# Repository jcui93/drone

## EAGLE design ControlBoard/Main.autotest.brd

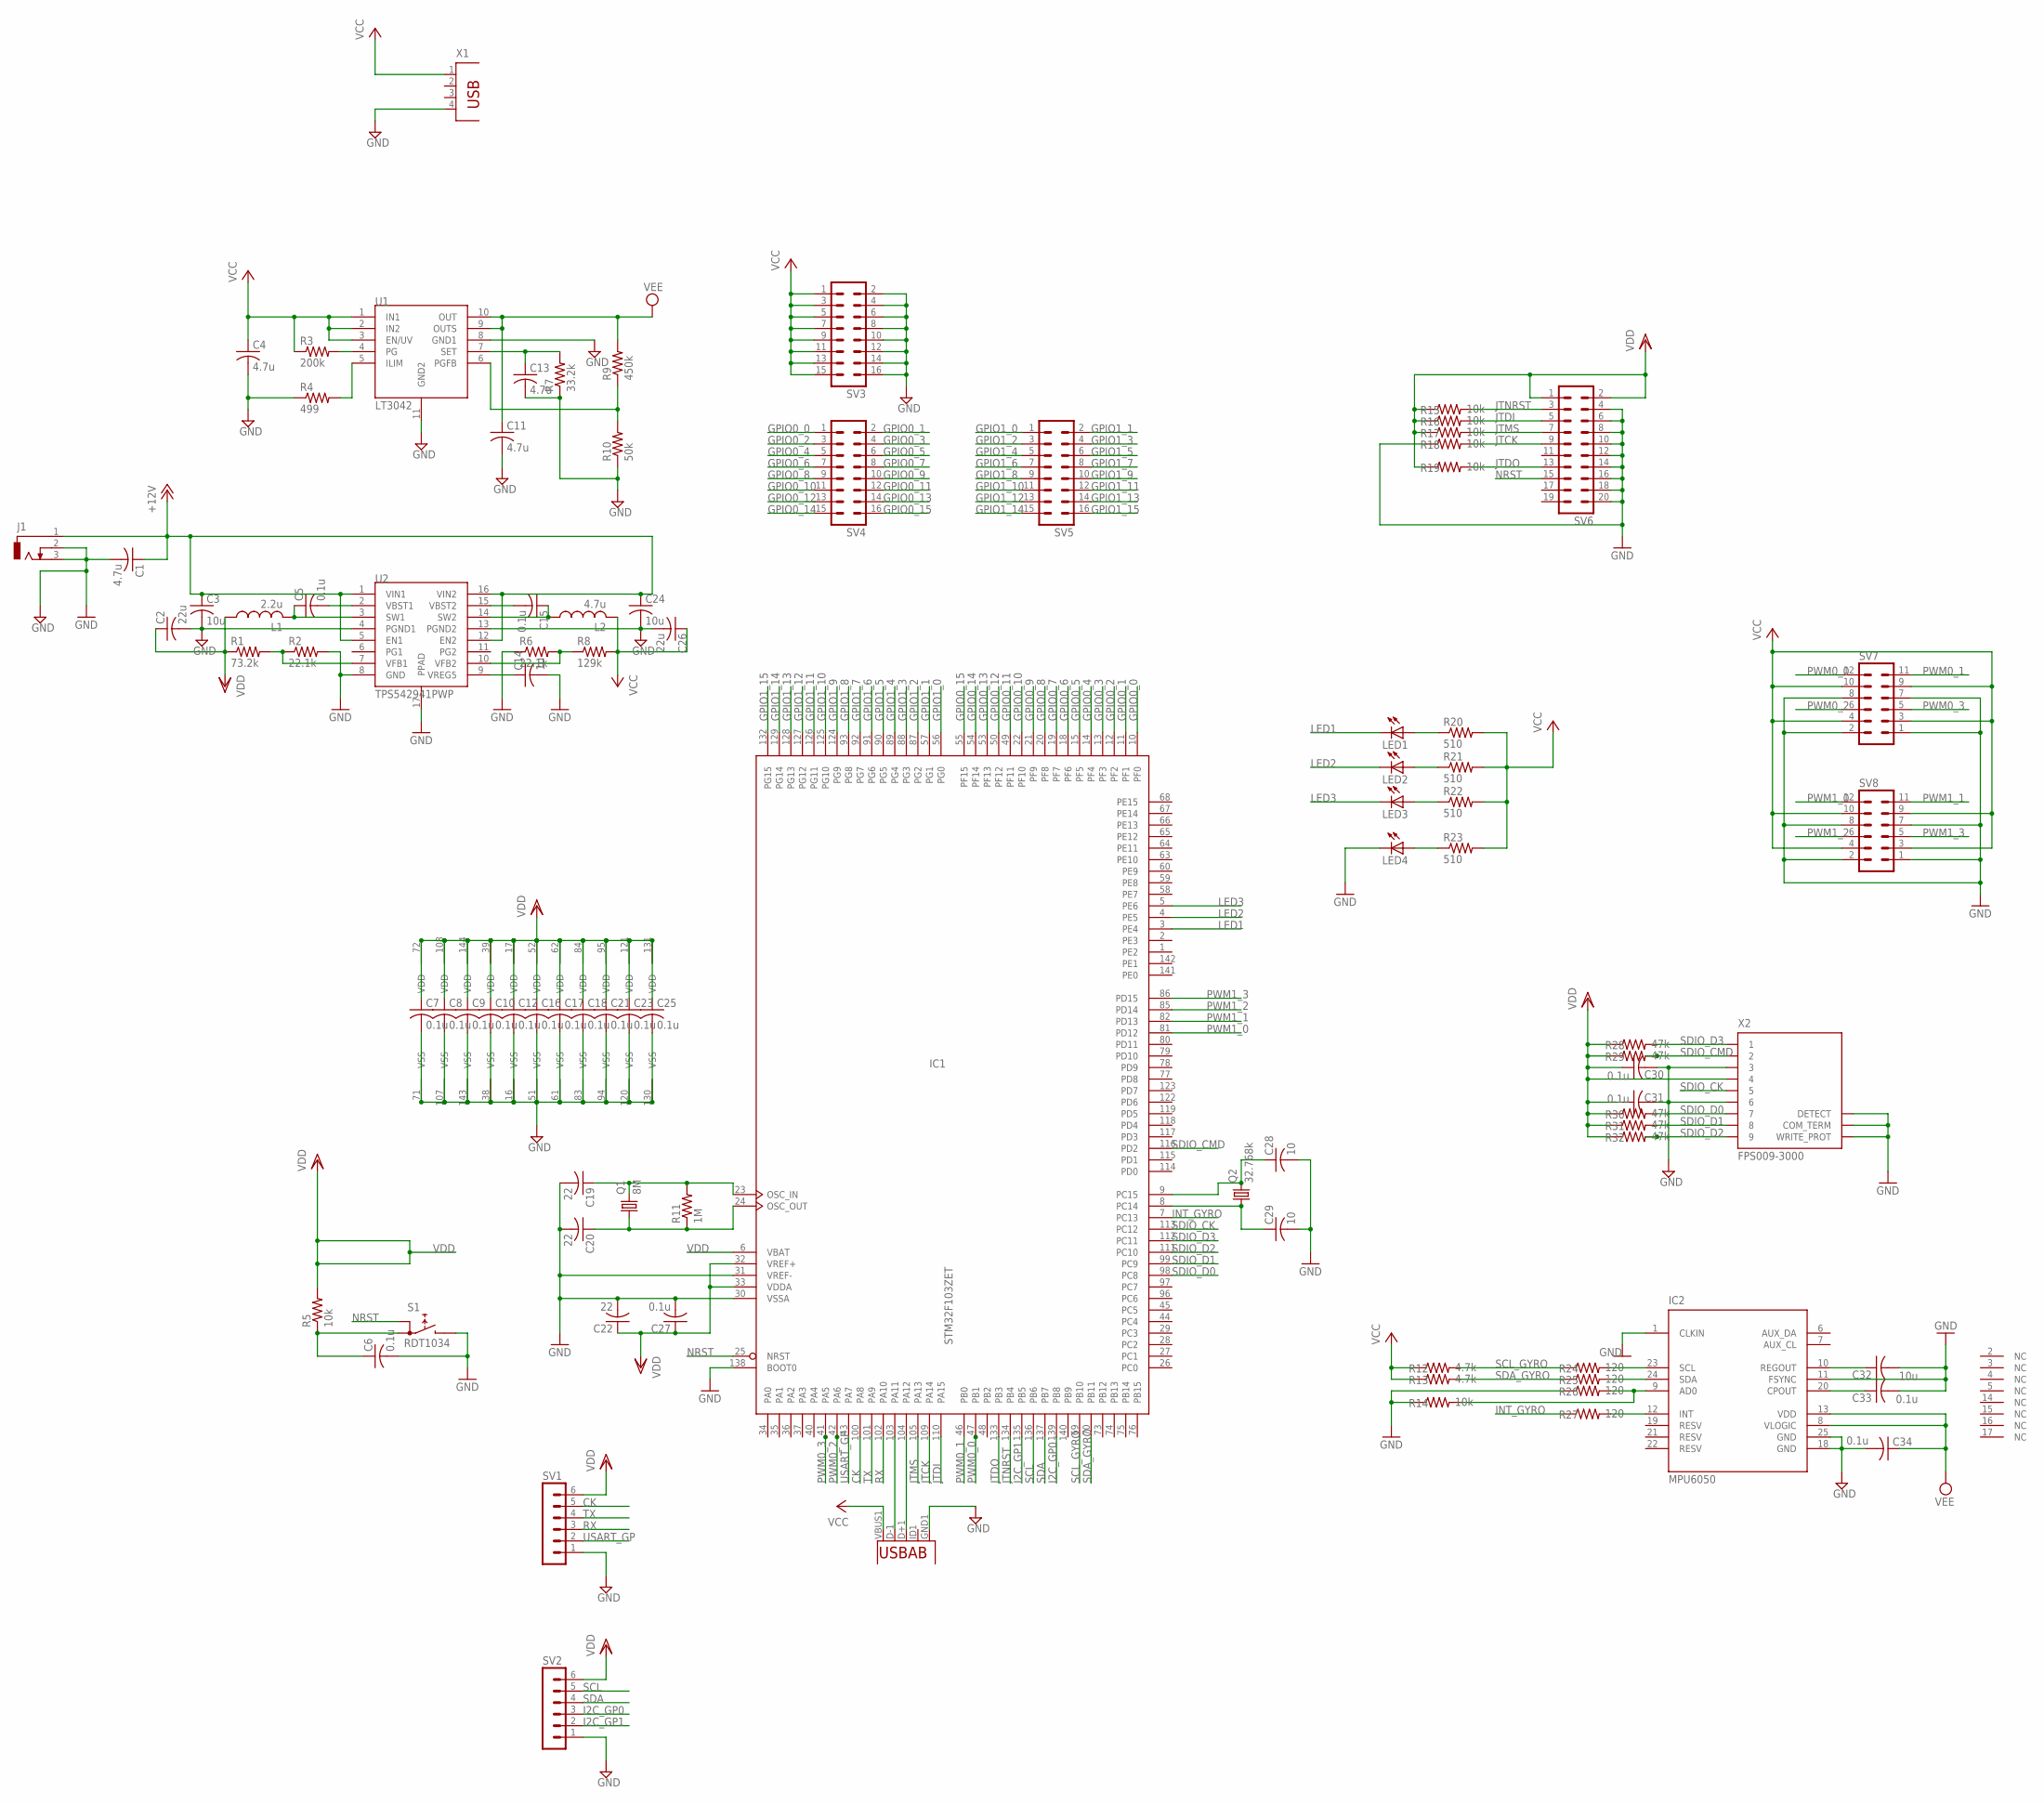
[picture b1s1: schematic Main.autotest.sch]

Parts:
C1: 4.7u; C1206
C2, C26: 22u; C0603
C3, C24, C32: 10u; C0603
C4, C11, C13: 4.7u; C0603
C5, C6, C7, C8, C9, C10, C12, C15, C16, C17, C18, C21, C23, C25, C27, C30, C31, C33, C34: 0.1u; C0603
C14: 1u; C0603
C19, C20, C22: 22; C0603
C28, C29: 10; C0603
IC1: STM32F103ZET; LQFP144
IC2: MPU6050; QFN50P400X400X95-25T265X275N
J1: DCJ0303
L1: 2.2u; L1812
L2: 4.7u; L1812
LED1, LED2, LED3, LED4: LED_E; LED_1206
Q1: 8M; HC49UP
Q2: 32.768k; HC49UP
R1: 73.2k; R1206
R2, R6: 22.1k; R1206
R3: 200k; R0603
R4: 499; R0603
R5, R14, R15, R16, R17, R18, R19: 10k; R0603
R7: 33.2k; R0603
R8: 129k; R1206
R9: 450k; R0603
R10: 50k; R0603
R11: 1M; R0603
R12, R13: 4.7k; R0603
R20, R21, R22, R23: 510; R0603
R24, R25, R26, R27: 120; R0603
R28, R29, R30, R31, R32: 47k; R0603
S1: RDT1034
SV1, SV2: MA06-1
SV3, SV4, SV5: MA08-2
SV6: MA10-2
SV7, SV8: MA06-2
U1: LT3042
U2: TPS542941PWP; HTSSOP16
U3: USB""; USB-MICRO-SMD
X1: PN87520
X2: FPS009-3000

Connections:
+12V: C1.1, C3.1, C24.1, J1.1, U2.1 (VIN1), U2.5 (EN1), U2.12 (EN2), U2.16 (VIN2)
CK: IC1.100 (PA8), SV1.5
GND: C1.2, C2.2, C3.2, C4.2, C6.2, C7.2, C8.2, C9.2, C10.2, C11.2, C12.2, C13.2, C14.2, C16.2, C17.2, C18.2, C19.2, C20.2, C21.2, C22.2, C23.2, C24.2, C25.2, C26.2, C27.2, C28.2, C29.2, C30.2, C31.2, C32.2, C33.2, C34.2, IC1.16 (VSS), IC1.30 (VSSA), IC1.31 (VREF-), IC1.38 (VSS), IC1.51 (VSS), IC1.61 (VSS), IC1.71 (VSS), IC1.83 (VSS), IC1.94 (VSS), IC1.107 (VSS), IC1.120 (VSS), IC1.130 (VSS), IC1.138 (BOOT0), IC1.143 (VSS), IC2.1 (CLKIN), IC2.11 (FSYNC), IC2.18 (GND), IC2.25 (GND), J1.2, J1.3, LED4.C, R2.2, R4.1, R6.1, R7.1, R10.1, R14.1, R18.1, R26.1, S1.B, SV1.1, SV2.1, SV3.2, SV3.4, SV3.6, SV3.8, SV3.10, SV3.12, SV3.14, SV3.16, SV6.4, SV6.6, SV6.8, SV6.10, SV6.12, SV6.14, SV6.16, SV6.18, SV6.20, SV7.1, SV7.2, SV7.7, SV7.8, SV8.1, SV8.2, SV8.7, SV8.8, U1.8 (GND1), U1.11 (GND2), U2.4 (PGND1), U2.8 (GND), U2.13 (PGND2), U2.17 (PPAD), U3.GND1 (GND), X1.4, X2.3, X2.6, X2.COM_TERM, X2.DETECT, X2.WRITE_PROT
GPIO0_0: IC1.10 (PF0), SV4.1
GPIO0_1: IC1.11 (PF1), SV4.2
GPIO0_2: IC1.12 (PF2), SV4.3
GPIO0_3: IC1.13 (PF3), SV4.4
GPIO0_4: IC1.14 (PF4), SV4.5
GPIO0_5: IC1.15 (PF5), SV4.6
GPIO0_6: IC1.18 (PF6), SV4.7
GPIO0_7: IC1.19 (PF7), SV4.8
GPIO0_8: IC1.20 (PF8), SV4.9
GPIO0_9: IC1.21 (PF9), SV4.10
GPIO0_10: IC1.22 (PF10), SV4.11
GPIO0_11: IC1.49 (PF11), SV4.12
GPIO0_12: IC1.50 (PF12), SV4.13
GPIO0_13: IC1.53 (PF13), SV4.14
GPIO0_14: IC1.54 (PF14), SV4.15
GPIO0_15: IC1.55 (PF15), SV4.16
GPIO1_0: IC1.56 (PG0), SV5.1
GPIO1_1: IC1.57 (PG1), SV5.2
GPIO1_2: IC1.87 (PG2), SV5.3
GPIO1_3: IC1.88 (PG3), SV5.4
GPIO1_4: IC1.89 (PG4), SV5.5
GPIO1_5: IC1.90 (PG5), SV5.6
GPIO1_6: IC1.91 (PG6), SV5.7
GPIO1_7: IC1.92 (PG7), SV5.8
GPIO1_8: IC1.93 (PG8), SV5.9
GPIO1_9: IC1.124 (PG9), SV5.10
GPIO1_10: IC1.125 (PG10), SV5.11
GPIO1_11: IC1.126 (PG11), SV5.12
GPIO1_12: IC1.127 (PG12), SV5.13
GPIO1_13: IC1.128 (PG13), SV5.14
GPIO1_14: IC1.129 (PG14), SV5.15
GPIO1_15: IC1.132 (PG15), SV5.16
I2C_GP0: IC1.139 (PB8), SV2.3
I2C_GP1: IC1.135 (PB5), SV2.2
INT_GYRO: IC1.7 (PC13), R27.1
JTCK: IC1.109 (PA14), R18.2, SV6.9
JTDI: IC1.110 (PA15), R16.2, SV6.5
JTDO: IC1.133 (PB3), R19.2, SV6.13
JTMS: IC1.105 (PA13), R17.2, SV6.7
JTNRST: IC1.134 (PB4), R15.2, SV6.3
LED1: IC1.3 (PE4), LED1.C
LED2: IC1.4 (PE5), LED2.C
LED3: IC1.5 (PE6), LED3.C
unnamed: C19.1, IC1.23 (OSC_IN), Q1.2, R11.2
unnamed: C20.1, IC1.24 (OSC_OUT), Q1.1, R11.1
unnamed: IC1.103 (PA11), U3.D-1 (D-)
unnamed: C29.1, IC1.8 (PC14), Q2.1
unnamed: C28.1, IC1.9 (PC15), Q2.2
unnamed: IC1.104 (PA12), U3.D+1 (D+)
unnamed: C6.1, R5.1, S1.A1
unnamed: LED4.A, R23.1
unnamed: LED1.A, R20.1
unnamed: IC2.23 (SCL), R24.2
unnamed: IC2.24 (SDA), R25.2
unnamed: LED2.A, R21.1
unnamed: C5.2, U2.2 (VBST1)
unnamed: IC2.12 (INT), R27.2
unnamed: C32.1, IC2.10 (REGOUT)
unnamed: C33.1, IC2.20 (CPOUT)
unnamed: IC2.9 (AD0), R14.2, R26.2
unnamed: LED3.A, R22.1
unnamed: C15.2, U2.15 (VBST2)
unnamed: C5.1, L1.2, U2.3 (SW1)
unnamed: R3.2, U1.4 (PG)
unnamed: C15.1, L2.1, U2.14 (SW2)
unnamed: R4.2, U1.5 (ILIM)
unnamed: R9.1, R10.2, U1.6 (PGFB)
unnamed: R1.2, R2.1, U2.7 (VFB1)
unnamed: C13.1, R7.2, U1.7 (SET)
unnamed: R6.2, R8.1, U2.10 (VFB2)
unnamed: C14.1, U2.9 (VREG5)
NRST: IC1.25 (NRST), S1.A, SV6.15
PWM0_0: IC1.47 (PB1), SV7.12
PWM0_1: IC1.46 (PB0), SV7.11
PWM0_2: IC1.42 (PA6), SV7.6
PWM0_3: IC1.41 (PA5), SV7.5
PWM1_0: IC1.81 (PD12), SV8.12
PWM1_1: IC1.82 (PD13), SV8.11
PWM1_2: IC1.85 (PD14), SV8.6
PWM1_3: IC1.86 (PD15), SV8.5
RX: IC1.102 (PA10), SV1.3
SCL: IC1.136 (PB6), SV2.5
SCL_GYRO: IC1.69 (PB10), R12.2, R24.1
SDA: IC1.137 (PB7), SV2.4
SDA_GYRO: IC1.70 (PB11), R13.2, R25.1
SDIO_CK: IC1.113 (PC12), X2.5
SDIO_CMD: IC1.116 (PD2), R29.2, X2.2
SDIO_D0: IC1.98 (PC8), R30.2, X2.7
SDIO_D1: IC1.99 (PC9), R31.2, X2.8
SDIO_D2: IC1.111 (PC10), R32.2, X2.9
SDIO_D3: IC1.112 (PC11), R28.2, X2.1
TX: IC1.101 (PA9), SV1.4
USART_GP: IC1.43 (PA7), SV1.2
VCC: C4.1, C26.1, L2.2, R3.1, R8.2, R12.1, R13.1, R20.2, R21.2, R22.2, R23.2, SV3.1, SV3.3, SV3.5, SV3.7, SV3.9, SV3.11, SV3.13, SV3.15, SV7.3, SV7.4, SV7.9, SV7.10, SV8.3, SV8.4, SV8.9, SV8.10, U1.1 (IN1), U1.2 (IN2), U1.3 (EN/UV), U3.VBUS1 (VBUS), X1.1
VDD: C2.1, C7.1, C8.1, C9.1, C10.1, C12.1, C16.1, C17.1, C18.1, C21.1, C22.1, C23.1, C25.1, C27.1, C30.1, C31.1, IC1.6 (VBAT), IC1.17 (VDD), IC1.32 (VREF+), IC1.33 (VDDA), IC1.39 (VDD), IC1.52 (VDD), IC1.62 (VDD), IC1.72 (VDD), IC1.84 (VDD), IC1.95 (VDD), IC1.108 (VDD), IC1.121 (VDD), IC1.131 (VDD), IC1.144 (VDD), L1.1, R1.1, R5.2, R15.1, R16.1, R17.1, R19.1, R28.1, R29.1, R30.1, R31.1, R32.1, SV1.6, SV2.6, SV6.1, SV6.2, X2.4
VEE: C11.1, C34.1, IC2.8 (VLOGIC), IC2.13 (VDD), R9.2, U1.9 (OUTS), U1.10 (OUT)

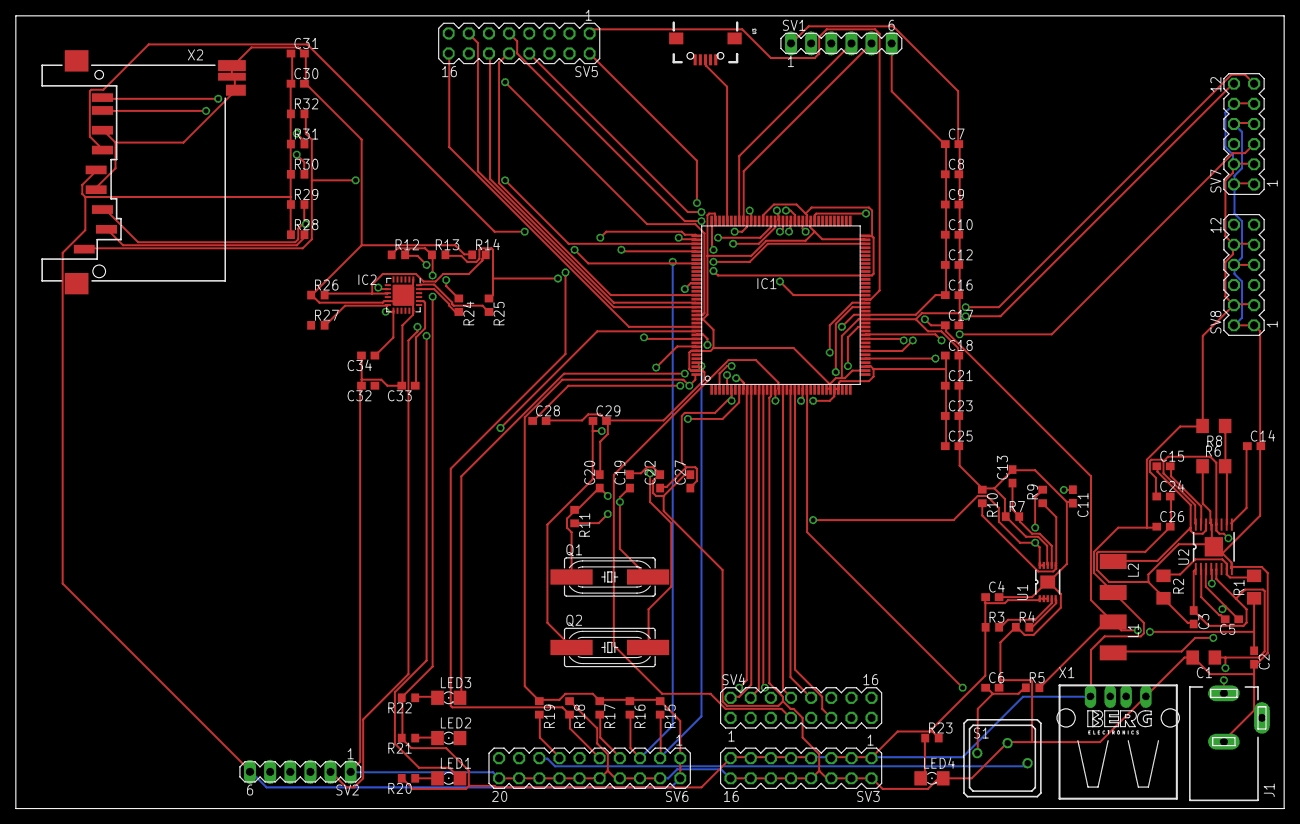
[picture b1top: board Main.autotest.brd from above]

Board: 4 copper layers, 160.0 x 100.0 mm, 91 parts (0 on the bottom side), 99 nets.

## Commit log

2016-08-17 Initialized Drone Project
2016-08-17 synced with saturn
2016-08-17 removed elev-8 v3 tools and documentation
2016-08-17 converted diagrams to jpg files
2016-08-17 renamed datasheet lt1765
